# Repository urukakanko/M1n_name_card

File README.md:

# M1n_name_card

砂川の個人名刺組立資料です

組立てると四足歩行ロボになります

# 回路図

# DEMO

組立後の動作画像
https://youtu.be/6SdT4taZKSw 
 
# Features

この名刺はクワッドクローラーの兄弟分です
https://bit-trade-one.co.jp/adcrbt/

# Requirement
 
Sipeed Maix NANO(N1n)　ラジオデパート1FのShigezoneで購入可能かも（品切れ必至）もしくはSeeedにて
https://www.shigezone.com/

サーボモータやロボットの脚などはビット・トレード・ワンでセットで購入可能
https://btoshop.jp/collections/educationrobot/products/adcr

# Author
Hiroyuki Sunagawa

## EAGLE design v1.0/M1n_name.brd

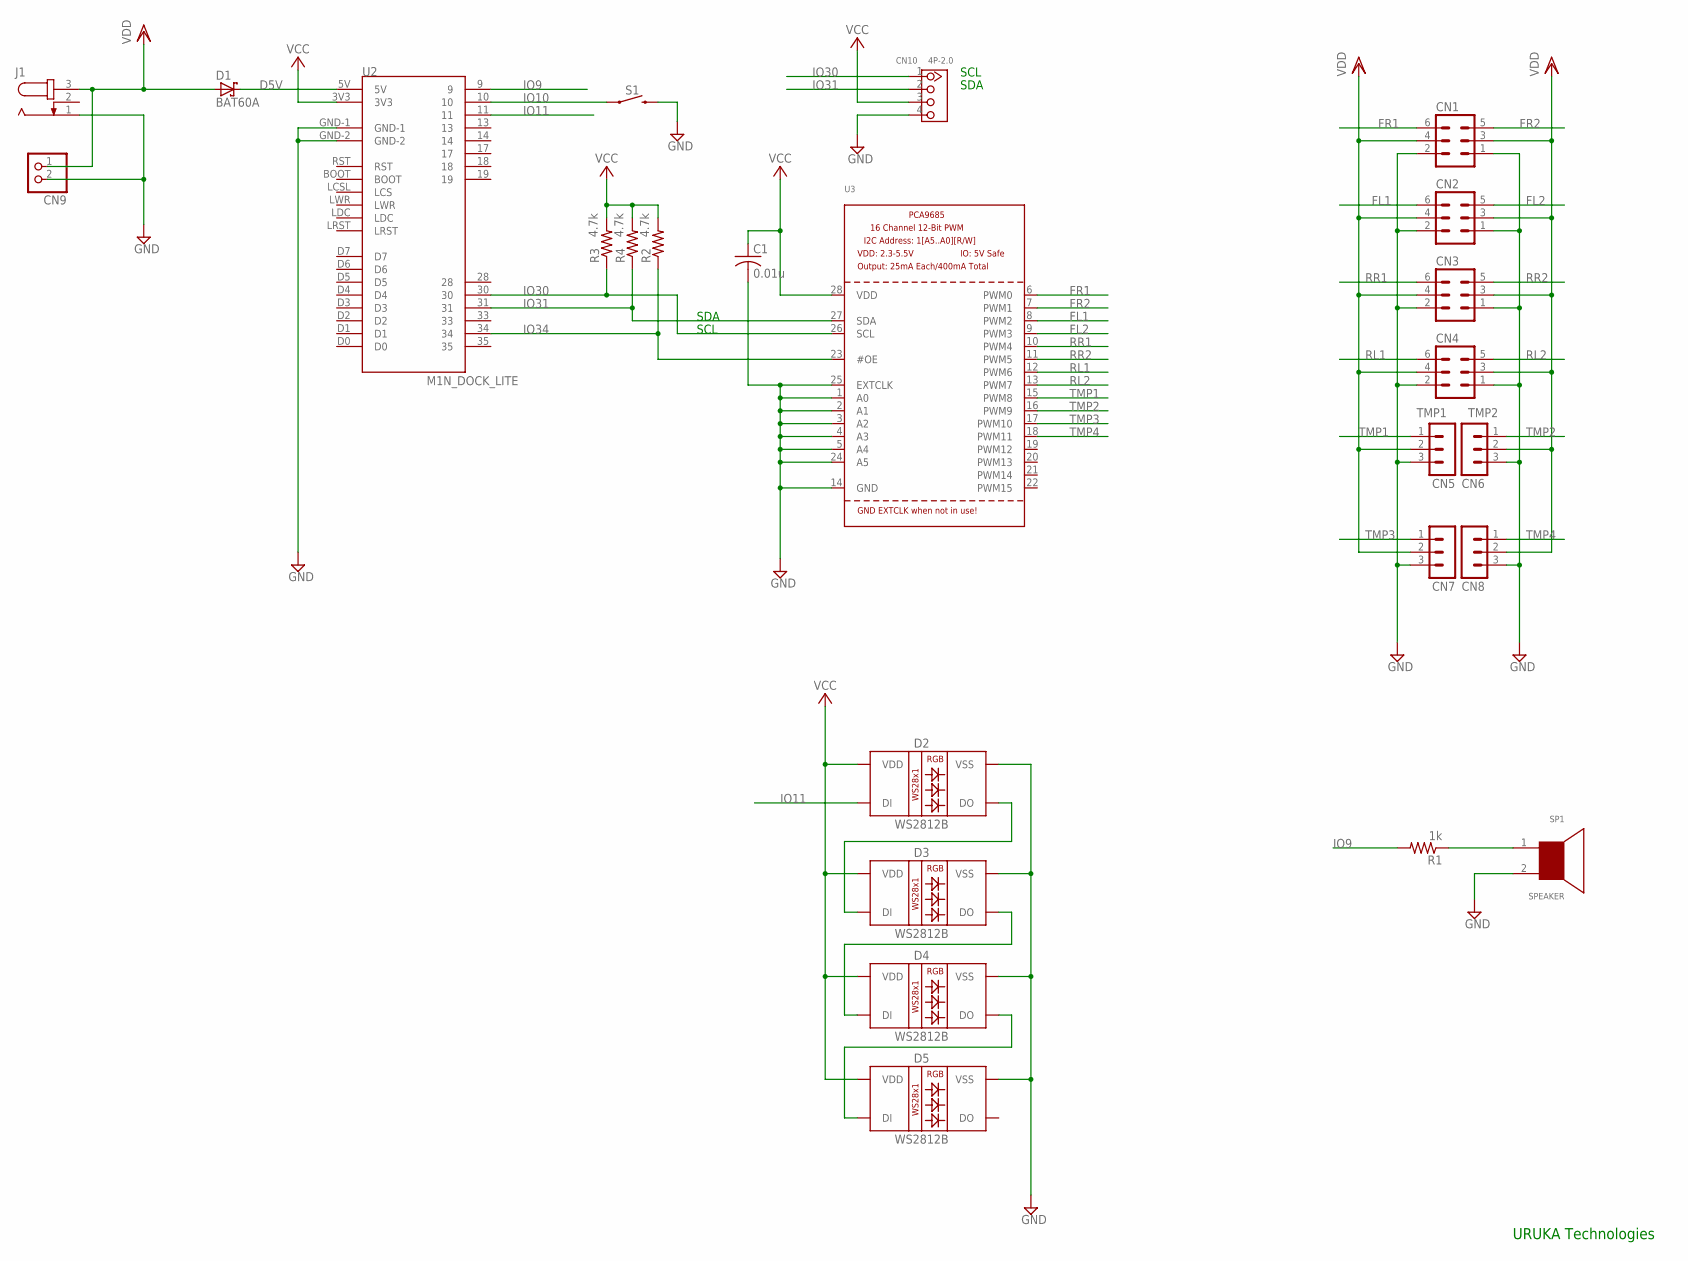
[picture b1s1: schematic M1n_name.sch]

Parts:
C1: 0.01u; C0603
CN1, CN2, CN3, CN4: MA03-2
CN5, CN6, CN7, CN8: MA03-1
CN9: JST_2PIN-THM; JST-PH-2-THM
CN10: 4P-2.0; HW4-2.0
D1: BAT60A; SOD323_ST
D2, D3, D4, D5: WS2812B; WS2812_2020
J1: JACK-PLUG0; SPC4077
R1: 1k; 0204/5
R2, R3, R4: 4.7k; 0204/5
S1: MOMENTARY-SWITCH-SPST-SMD-6.0X3.5MM; TACTILE_SWITCH_SMD_6.0X3.5MM
SP1: SPEAKER
U2: M1N_DOCK_LITE
U3: PCA9685; TSSOP28

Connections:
D5V: D1.C, U2.5V
FL1: CN2.6, U3.8 (PWM2)
FL2: CN2.5, U3.9 (PWM3)
FR1: CN1.6, U3.6 (PWM0)
FR2: CN1.5, U3.7 (PWM1)
GND: C1.2, CN1.1, CN1.2, CN2.1, CN2.2, CN3.1, CN3.2, CN4.1, CN4.2, CN5.3, CN6.3, CN7.3, CN8.3, CN9.2 (1), CN10.4, D2.2 (VSS), D3.2 (VSS), D4.2 (VSS), D5.2 (VSS), J1.1, S1.2, SP1.2, U2.GND-1, U2.GND-2, U3.1 (A0), U3.2 (A1), U3.3 (A2), U3.4 (A3), U3.5 (A4), U3.14 (GND), U3.24 (A5), U3.25 (EXTCLK)
IO9: R1.2, U2.9
IO10: S1.1, U2.10
IO11: D2.3 (DI), U2.11
IO30: CN10.1, R3.1, U2.30, U3.26 (SCL)
IO31: CN10.2, R4.1, U2.31, U3.27 (SDA)
IO34: R2.1, U2.34, U3.23 (#OE)
unnamed: D2.1 (DO), D3.3 (DI)
unnamed: D3.1 (DO), D4.3 (DI)
unnamed: D4.1 (DO), D5.3 (DI)
unnamed: R1.1, SP1.1
RL1: CN4.6, U3.12 (PWM6)
RL2: CN4.5, U3.13 (PWM7)
RR1: CN3.6, U3.10 (PWM4)
RR2: CN3.5, U3.11 (PWM5)
TMP1: CN5.1, U3.15 (PWM8)
TMP2: CN6.1, U3.16 (PWM9)
TMP3: CN7.1, U3.17 (PWM10)
TMP4: CN8.1, U3.18 (PWM11)
VCC: C1.1, CN10.3, D2.4 (VDD), D3.4 (VDD), D4.4 (VDD), D5.4 (VDD), R2.2, R3.2, R4.2, U2.3V3, U3.28 (VDD)
VDD: CN1.3, CN1.4, CN2.3, CN2.4, CN3.3, CN3.4, CN4.3, CN4.4, CN5.2, CN6.2, CN7.2, CN8.2, CN9.1 (2), D1.A, J1.3

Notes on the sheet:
URUKA Technologies
SCL
SDA

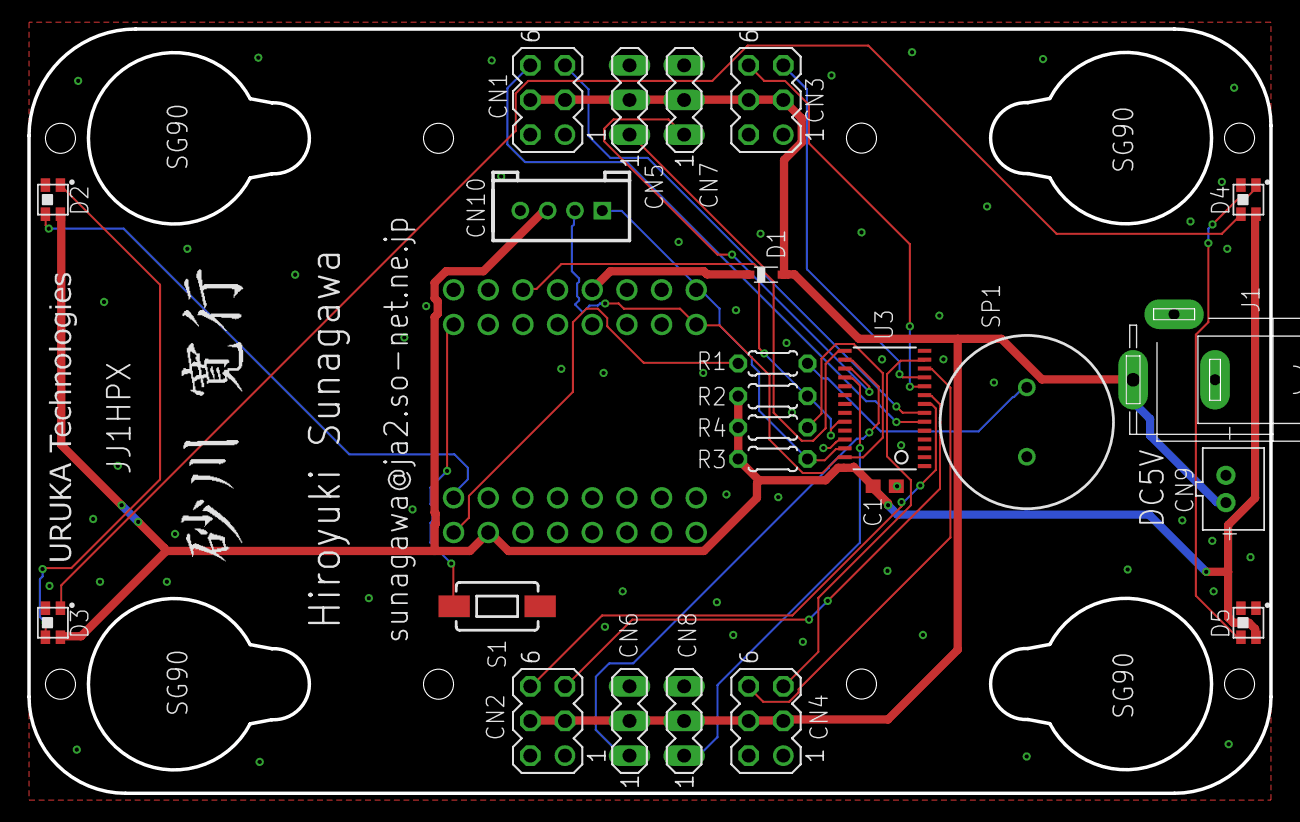
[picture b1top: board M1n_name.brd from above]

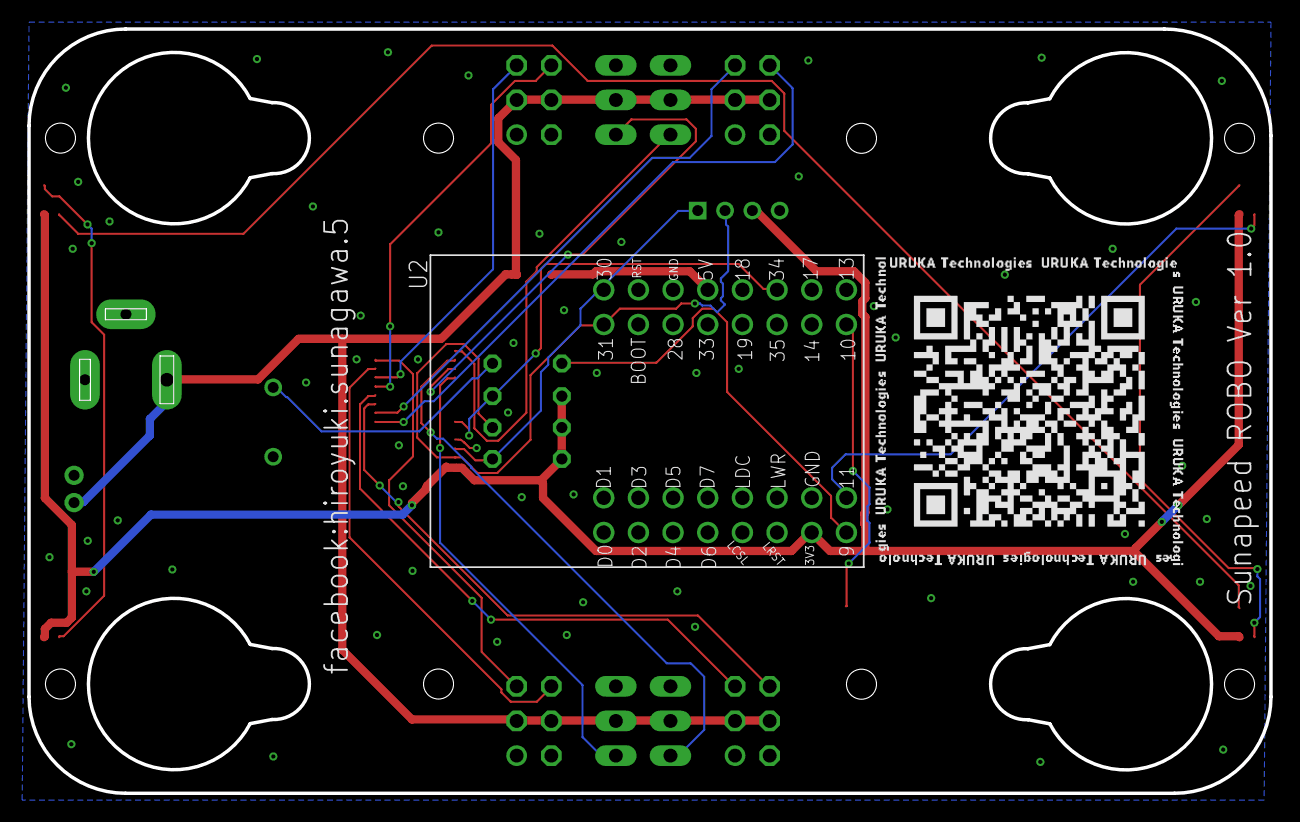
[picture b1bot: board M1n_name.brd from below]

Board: 2 copper layers, 91.0 x 56.0 mm, 32 parts (3 on the bottom side), 26 nets.

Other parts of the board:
U$4, U$5, U$6, U$7: SG90BASE
U$8: M1N_GIT
U$16: SUNA
U$17: URUKA

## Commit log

2020-03-25 Eagle file
    Eagle file

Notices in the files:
parts and their libraries:
SparkFun-Switches: Licensing: Creative Commons ShareAlike 4.0 International - https://creativecommons.org/licenses/by-sa/4.0
